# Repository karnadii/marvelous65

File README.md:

# Marvelous65 Keyboard Series
A 65% wireless hotswap keyboard with Rotary encoder, OLED display and RGB underglow.

## Marvelous65

## Marvelous65 Ergo

## Marvelous65 Split

# WARNING!!!
**FOR ADVANCED USER ONLY!!, THIS IS A DIY KEYBOARD AND NO ONE SELL IT, BUILDING THIS KEYBOARD REQUIRE YOU TO ORDER THE PCB FROM PCB MANU, SOLDER ALL THE COMPONENT YOURSELF, MAKING YOUR OWN PLATE AND CASE YOURSELF. IF YOU ONLY KNOW HOW TO ASSEMBLY A KEYBOARD, THIS IS NOT FOR YOU.**

This keyboard is inspired by luantty2's Candy BLE (https://github.com/luantty2/nRF52840-instruction). When I first saw that I was like "Beautiful! Marvelous!" but that would be nice to make that in 65%. So With no basic knowledge of electronic I brave myself to learn Kicad with the guide of https://wiki.ai03.com/. Basically this is just an nrfmicro 1.4 by Joric embedded in PCB. I also learn some basic Fusion 360 to make a keyboard case and plate.

When I finish designing this, I realize I am not he first one to design this, there is someone in zfrontier forum already done it, it is called Rainbow65, check it out https://www.zfrontier.com/app/flow/e1rpMAd9Nz75.
and there is someone planning an IC for similar layout and feature. 

## Bootloader
Before flashing the firmware, you have to flash the bootloader first. Follow the nrfmicro guide to flash the bootloader https://github.com/joric/nrfmicro/wiki/Bootloader
## Firmware
The firmware will use [ZMK](https://zmkfirmware.dev/). Basic setup ZMK firmware https://zmkfirmware.dev/docs/development/setup.
copy the firmware file to `app/boards/shields`. Edit the keymap or any other feature as you want and build the firmware using the following command 
```bash
west build -p -b nrfmicro_13 -- -DSHIELD=marvelous65_rev2
west build -p -b nrfmicro_13 -- -DSHIELD=marvelous65_ergo
west build -p -b nrfmicro_13 -- -DSHIELD=marvelous65_split_right
west build -p -b nrfmicro_13 -- -DSHIELD=marvelous65_split_left
```

## Features
- Dual mode wireless and wired
- rotary encoder
- oled display 
- rgb underglow
- hotswap (except split version)
- multilayout (except ergo version)

## PCB 
the marvelous65 standard and split version I route it manually. the ergo version I semi auto route it with freerouting. I know a little about electronic, if you have some suggestion or want to coorect the PCB/schematic feel free to make a PR or open an issue.
### Marvelous65

### Marvelous65 Ergo

### Marvelous65 Split

## Layout
### Marvelous65

try it in [KLE](http://www.keyboard-layout-editor.com/##@_name=marvelous65%3B&@_x:3%3B&=~%0A%60&=!%0A1&=%2F@%0A2&=%23%0A3&=$%0A4&=%25%0A5&=%5E%0A6&=%2F&%0A7&=*%0A8&=(%0A9&=)%0A0&=%2F_%0A-&=+%0A%2F=&_a:6&w:2%3B&=Back&_x:0.25%3B&=enc1&_x:1&a:7%3B&=&=%3B&@_x:3&a:4&w:1.5%3B&=Tab&=Q&=W&=E&=R&=T&=Y&=U&=I&=O&=P&=%7B%0A%5B&=%7D%0A%5D&_w:1.5%3B&=%7C%0A%5C&_x:3&a:7&w:1.25&h:2&w2:1.5&h2:1&x2:-0.25%3B&=%3B&@_a:4&w:1.25&w2:1.75&l:true%3B&=Caps%20Lock&_x:1.75&w:1.75%3B&=Caps%20Lock&=A&=S&=D&=F&=G&=H&=J&=K&=L&=%2F:%0A%2F%3B&=%22%0A'&_a:6&w:2.25%3B&=Enter&_x:2&a:7%3B&=%3B&@_w:1.25%3B&=&=&_x:0.75&a:6&w:2.25%3B&=Shift&_a:4%3B&=Z&=X&=C&=V&=B&=N&=M&=%3C%0A,&=%3E%0A.&=%3F%0A%2F%2F&_a:6&w:1.75%3B&=Shift%3B&@_y:-0.75&x:17.25&a:7%3B&=%E2%86%91%3B&@_y:-0.25&x:3&a:6&w:1.25%3B&=Ctrl&_w:1.25%3B&=Win&_w:1.25%3B&=Alt&_a:7&w:6.25%3B&=&_a:6%3B&=Alt&=Fn&=Ctrl%3B&@_y:-0.75&x:16.25&a:7%3B&=%E2%86%90&=%E2%86%93&=%E2%86%92%3B&@_x:6.75&w:2.25%3B&=&_w:1.25%3B&=&_w:2.75%3B&=&_w:1.5%3B&=&_w:1.5%3B&=) (Support ISO, stplit backspace, split spacebar, stepped caps)

### Marvelous65 Ergo

try it in [KLE](http://www.keyboard-layout-editor.com/##@_name=Marvelous65%20Ergo%3B&@_y:0.2&x:2.75%3B&=%2F@%0A2&_x:8.75%3B&=%2F_%0A-%3B&@_y:-0.95&x:0.75%3B&=~%0A%60&=!%0A1&_x:10.75%3B&=+%0A%2F=&_a:6&w:2%3B&=Backspace&_x:0.75%3B&=ENC%3B&@_y:-0.050000000000000044&x:12.25&a:4%3B&=P%3B&@_y:-0.9500000000000002&x:0.5&w:1.5%3B&=Tab&=Q&_x:10.25%3B&=%7B%0A%5B&=%7D%0A%5D&_w:1.5%3B&=%7C%0A%5C%3B&@_x:0.25&w:1.75%3B&=Caps%20Lock&=A&_x:9.75%3B&=%2F:%0A%2F%3B&=%22%0A'&_a:6&w:2.25%3B&=Enter%3B&@_w:2.25%3B&=Shift&_a:4%3B&=Z&_x:9%3B&=%3E%0A.&=%3F%0A%2F%2F&_a:6&w:1.75%3B&=Shift%3B&@_y:-0.75&x:16.25&a:7%3B&=%E2%86%91%3B&@_y:-0.25&a:6&w:1.25%3B&=Ctrl&_w:1.25%3B&=Win&_x:10&a:7&w:1.25%3B&=&_w:1.25%3B&=%3B&@_y:-0.75&x:15.25%3B&=%E2%86%90&=%E2%86%93&=%E2%86%92%3B&@_r:12&rx:3.05&ry:4.35&y:-1.0999999999999996&x:0.20000000000000018&a:4%3B&=X&=C&=V&=B%3B&@_x:0.20000000000000018&a:7&w:1.25%3B&=&_w:2.75%3B&=%3B&@_rx:3.15&ry:3.35&y:-1.1&x:-0.1499999999999999&a:4%3B&=S&=D&=F&=G%3B&@_rx:3.25&ry:2.35&y:-1.1&x:-0.25%3B&=W&=E&=R&=T%3B&@_rx:3.35&ry:1.35&y:-1.1&x:0.3999999999999999%3B&=%23%0A3&=$%0A4&=%25%0A5&=%5E%0A6%3B&@_r:-12&rx:12.1&y:-1.1&x:-3.5999999999999996%3B&=%2F&%0A7&=*%0A8&=(%0A9&=)%0A0%3B&@_rx:12.2&ry:2.35&y:-1.1&x:-3.9499999999999993%3B&=Y&=U&=I&=O%3B&@_rx:12.3&ry:3.35&y:-1.1&x:-3.5500000000000007%3B&=H&=J&=K&=L%3B&@_rx:12.4&ry:4.35&y:-1.0999999999999996&x:-4.15&a:7%3B&=&_a:4%3B&=N&=M&=%3C%0A,%3B&@_rx:12.525&ry:5.5415&y:-1.2915&x:-4.025&a:7&w:2.25%3B&=&_w:1.25%3B&=) (Support split backspace and stepped caps) 

### Marvelous65 Split

try in in [KLE](http://www.keyboard-layout-editor.com/##@_name=Marvelous%20split%3B&@_x:18.25&a:6&w:2%3B&=Backspace%3B&@_x:2.25%3B&=L%2F_ENC&_x:0.25&a:4%3B&=~%0A%60&=!%0A1&=%2F@%0A2&=%23%0A3&=$%0A4&=%25%0A5&=%5E%0A6&_x:1.75%3B&=%2F&%0A7&=*%0A8&=(%0A9&=)%0A0&=%2F_%0A-&=+%0A%2F=&_a:7%3B&=&=&_x:0.25&a:6%3B&=R%2F_ENC%3B&@_x:3.5&a:4&w:1.5%3B&=Tab&=Q&=W&=E&=R&=T&_x:1.75%3B&=Y&=U&=I&=O&=P&=%7B%0A%5B&=%7D%0A%5D&_w:1.5%3B&=%7C%0A%5C&_x:2.75&a:7&w:1.25&h:2&w2:1.5&h2:1&x2:-0.25%3B&=%3B&@_a:6&w:1.25&w2:1.75&l:true%3B&=Cap&_x:2.25&a:4&w:1.75%3B&=Caps%20Lock&=A&=S&=D&=F&=G&_x:1.75%3B&=H&=J&=K&=L&=%2F:%0A%2F%3B&=%22%0A'&_a:6&w:2.25%3B&=Enter&_x:1.75&a:7%3B&=%3B&@_a:6&w:2.25%3B&=Shift&_x:1.25&a:7&w:1.25%3B&=&=&_a:4%3B&=Z&=X&=C&=V&=B&_x:1.75%3B&=N&=M&=%3C%0A,&=%3E%0A.&=%3F%0A%2F%2F&_a:6&w:1.75%3B&=Shift%3B&@_y:-0.75&x:19.5&a:7%3B&=%E2%86%91%3B&@_y:-0.25&x:3.5&a:6&w:1.25%3B&=Ctrl&_w:1.25%3B&=Win&_w:1.25%3B&=Alt&_a:7&w:2.25%3B&=&_w:1.25%3B&=&_x:1.75&w:2.75%3B&=&_a:6%3B&=Alt&=Fn&=Ctrl%3B&@_y:-0.75&x:18.5&a:7%3B&=%E2%86%90&=%E2%86%93&=%E2%86%92%3B&@_x:15.25&w:1.5%3B&=&_w:1.5%3B&=) (Support ISO, stplit backspace, split spacebar, stepped caps)

## Case
All the case is all 3d printed, except the ergo version have acrylic version case. The case have 3 part, top, middle and bottom. the top and bottom using PLA with 20% infill, while the middle use transparent PLA with 100% infill(to diffuse the underglow RGB) I only know some basic 3d knowledge, so if my case is not to your liking you can design your own case and make a PR or keep it to yourself. Here some rendered Image from fusion 360. The case is top mount. Using M2x5/M2x6 threaded insert and M2 screw (I don't remember the exact size, just buy a set of m2 screw.) The plate for marvelous65 and marvelous65 ergo is sandwiched between top case and bottom case, 

### Marvelous65

### Marvelous65 Ergo
#### Acrylic case

#### 3d printed case

### Marvelous65 Split
I am too lazy while designing this one, so I only design ANSI layout case. The plate is integrated to the case, so if you want different layout you want to make another case.

## GIF

https://user-images.githubusercontent.com/18657277/117118259-c4ab1200-adba-11eb-80a2-d7a4a54a5487.mp4

https://user-images.githubusercontent.com/18657277/117118099-8dd4fc00-adba-11eb-8657-396213f3611c.mp4

## BOM
See BOM file for JLCPCB in release page.
also I added IBOM for reference when you will solder it yourself

Marvelous65 IBOM https://karnadii.github.io/marvelous65/Marvelous65/Hardware/bom/ibom.html

Marvelous65-ergo IBOM https://karnadii.github.io/marvelous65/Marvelous65-ergo/Hardware/bom/ibom.html

Marvelous65-split IBOM https://karnadii.github.io/marvelous65/Marvelous65-split/Hardware/bom/ibom.html

## Battery
any lipo battery will do, i use 2.4 JST XH connector. it is better to use 3mm thickness battery.

for the pcb [JST XH2.54 Right Angle Pin Header Connector 2P](https://www.aliexpress.com/item/33008489410.html?spm=a2g0o.productlist.0.0.3fc04e79tqtraW&algo_pvid=cc25e59e-b91b-4300-889b-37802f464f64&algo_expid=cc25e59e-b91b-4300-889b-37802f464f64-14&btsid=0bb0620316222031400651818ee7d1&ws_ab_test=searchweb0_0,searchweb201602_,searchweb201603_)
for battery [JST XH 2PIN male](https://www.aliexpress.com/item/32996835431.html?spm=a2g0o.productlist.0.0.52173629BM0hSB&algo_pvid=e2dc7462-9258-4ca2-80d9-968e44934c82&algo_expid=e2dc7462-9258-4ca2-80d9-968e44934c82-4&btsid=0bb0622f16222032556806705ee066&ws_ab_test=searchweb0_0,searchweb201602_,searchweb201603_).
All the battery that I purchase have no connector/socket, so I have to solder it myself. Be carefull when soldering, pay attention to the negative and positive of the battery.

I am using this battery. Ignore the label the actual size is 3300mAh.

## TODO
- add acrylic case version
- add multi layout case for split version
- fix ergo version plate (misaligned one screw hole)
- marvelous65 ergo 3d printed case split version
- designing logo and silkscreen
- add assembly guide

## Support Me
Help me order prototype PCB for next revision

## Reference 
- nrfmicro 1.4 https://github.com/joric/nrfmicro/wiki
- nice60 pcb https://github.com/Nicell/nice60
- ZMK firmware https://github.com/zmkfirmware/zmk

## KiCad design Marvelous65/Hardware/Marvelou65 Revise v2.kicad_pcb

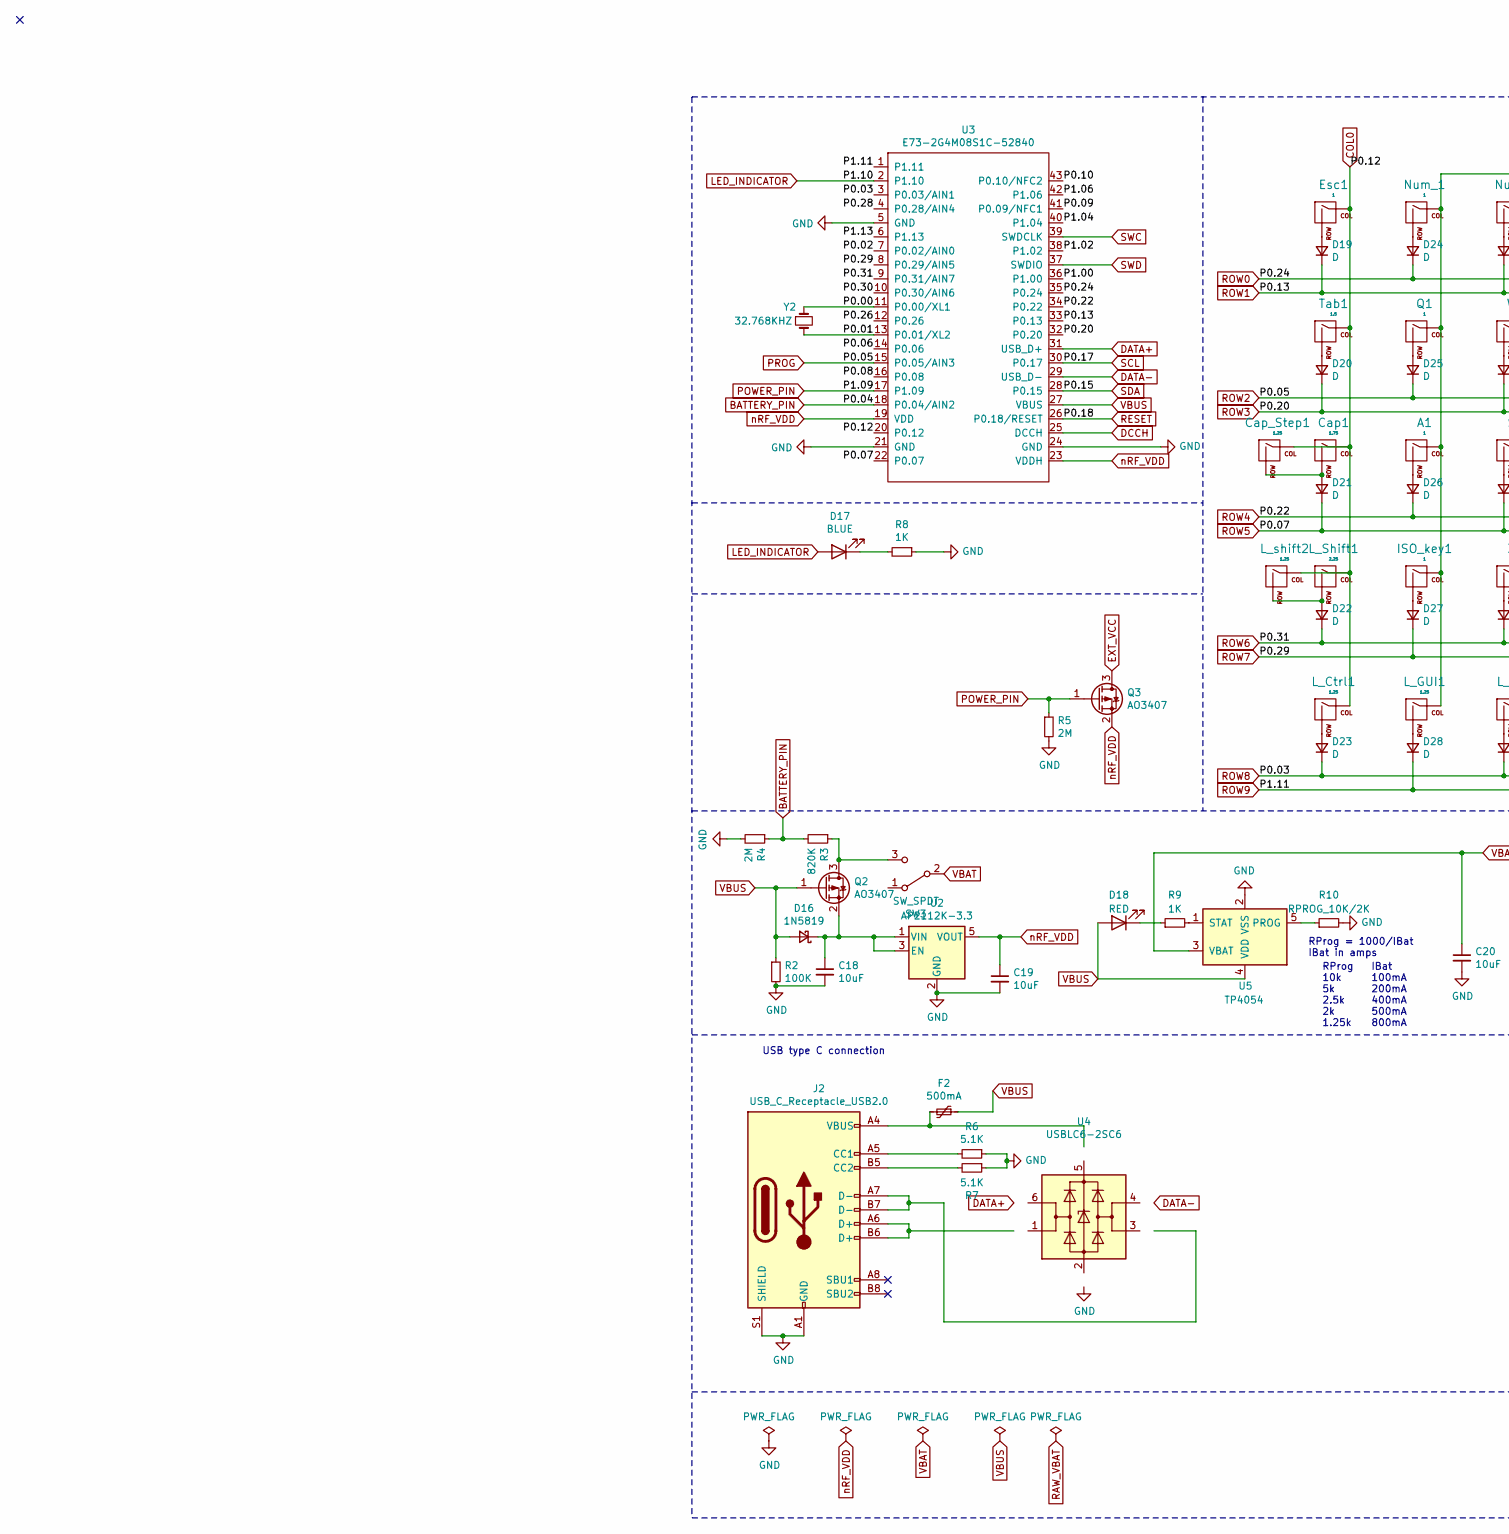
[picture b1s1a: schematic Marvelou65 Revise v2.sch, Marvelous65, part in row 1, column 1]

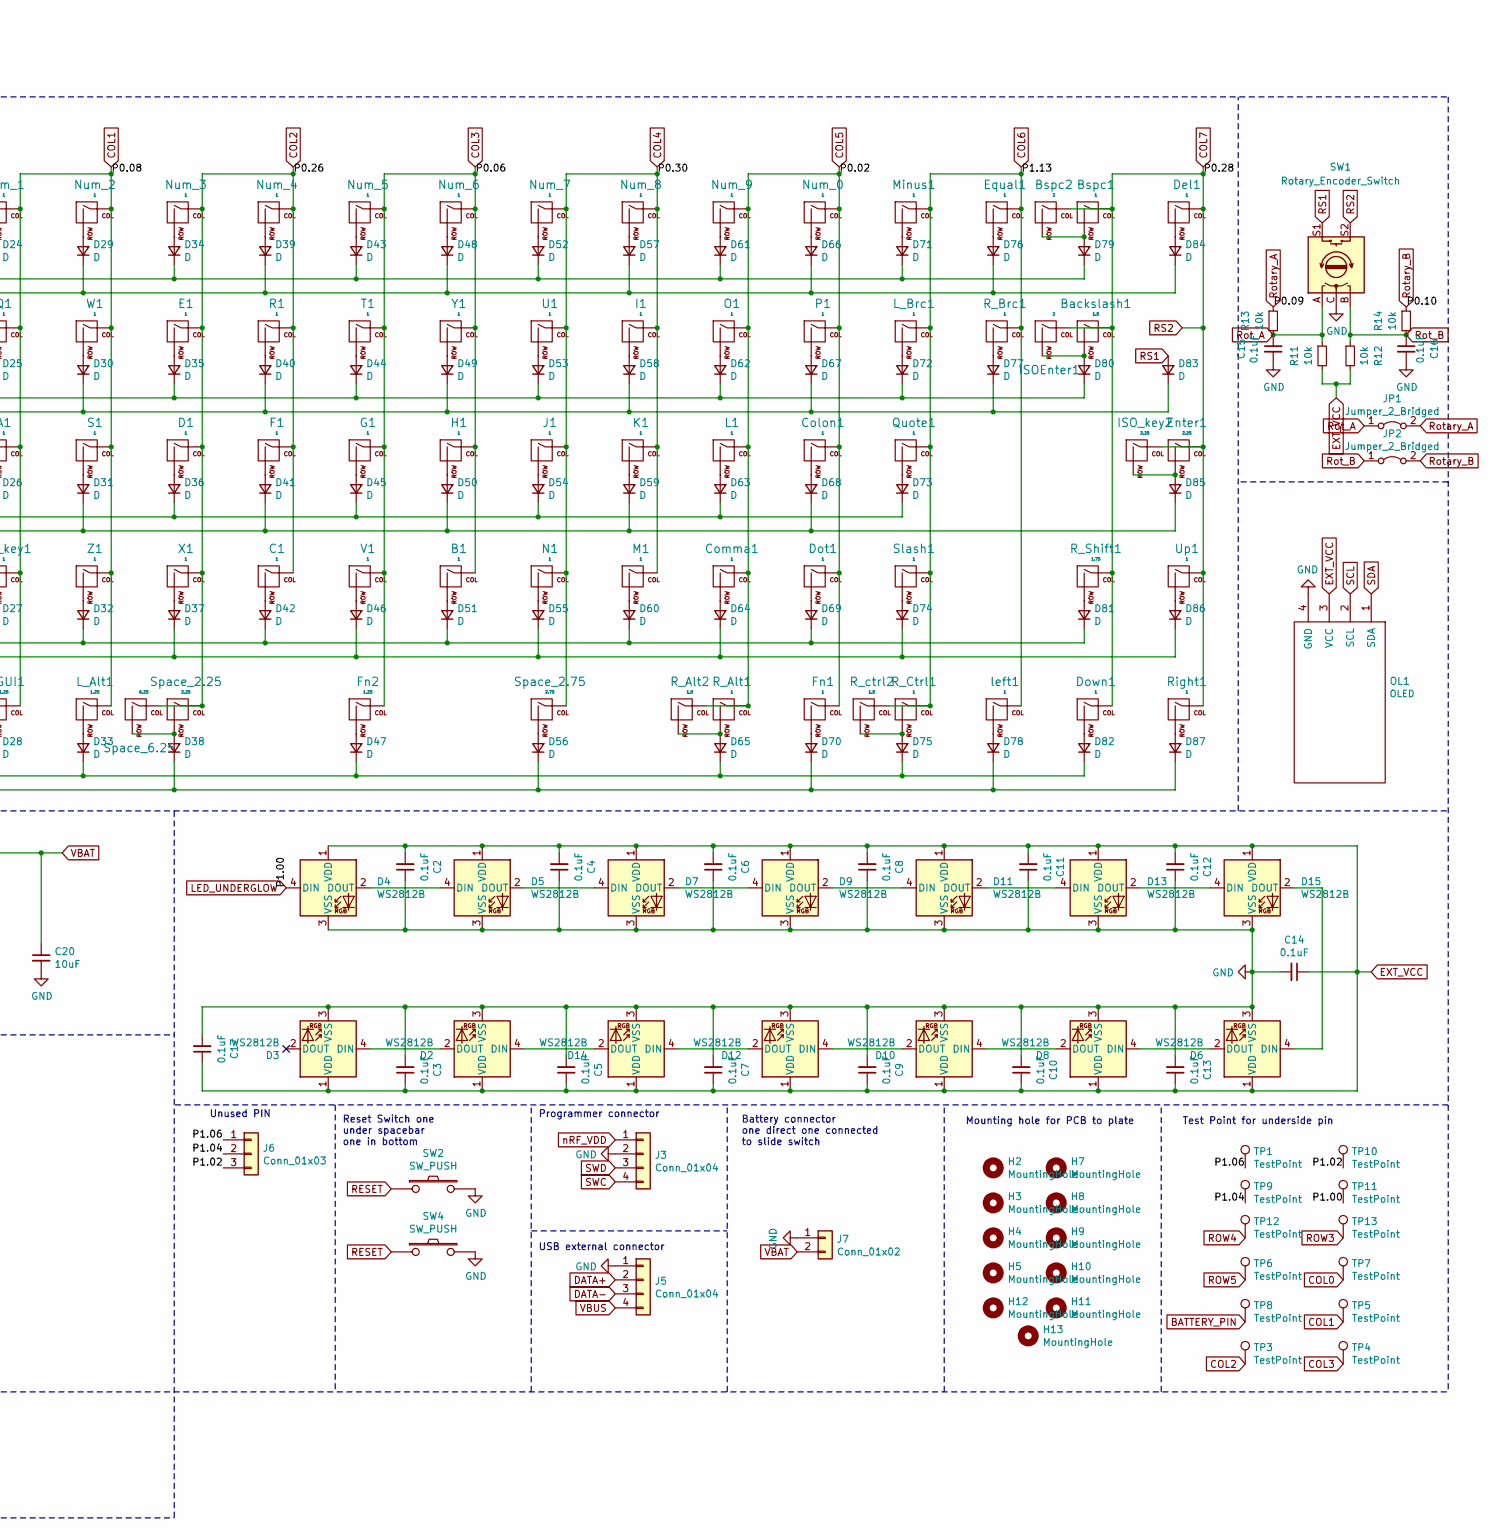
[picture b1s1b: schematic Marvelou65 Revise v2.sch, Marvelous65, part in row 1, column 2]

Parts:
A1: 1; MXOnly-1U-Hotswap
B1: 1; MXOnly-1U-Hotswap
Backslash1: 1.5; MXOnly-1.5U-Hotswap
Bspc1: 1; MXOnly-1U-Hotswap
Bspc2: 2; MXOnly-2U-Hotswap
C1: 1; MXOnly-1U-Hotswap
C2, C3, C4, C5, C6, C7, C8, C9, C10, C11, C12, C13, C14, C15, C16, C17: 0.1uF; C_0805_2012Metric_Pad1.15x1.40mm_HandSolder; LCSC Part Number C49678
C18, C19, C20: 10uF; C_0805_2012Metric_Pad1.15x1.40mm_HandSolder; LCSC Part Number C15850
Cap1: 1.75; MXOnly-1.75U-Hotswap
Cap_Step1: 1.25; MXOnly-1.25U-Hotswap
Colon1: 1; MXOnly-1U-Hotswap
Comma1: 1; MXOnly-1U-Hotswap
D1: 1; MXOnly-1U-Hotswap
D2, D3, D4, D5, D6, D7, D8, D9, D10, D11, D12, D13, D14, D15: WS2812B; LED_WS2812B_PLCC4_5.0x5.0mm_P3.2mm; LCSC Part Number C114586
D16: 1N5819; D_SOD-123; LCSC Part Number C169540
D17: BLUE; LED_0603_1608Metric_Pad1.05x0.95mm_HandSolder; LCSC Part Number C375446
D18: RED; LED_0603_1608Metric_Pad1.05x0.95mm_HandSolder; LCSC Part Number C375450
D19, D20, D21, D22, D23, D24, D25, D26, D27, D28, D29, D30, D31, D32, D33, D34, D35, D36, D37, D38, D39, D40, D41, D42, D43, D44, D45, D46, D47, D48, D49, D50, D51, D52, D53, D54, D55, D56, D57, D58, D59, D60, D61, D62, D63, D64, D65, D66, D67, D68, D69, D70, D71, D72, D73, D74, D75, D76, D77, D78, D79, D80, D81, D82, D83, D84, D85, D86, D87: D; D_SOD-123; LCSC Part Number C81598
Del1: 1; MXOnly-1U-Hotswap
Dot1: 1; MXOnly-1U-Hotswap
Down1: 1; MXOnly-1U-Hotswap
E1: 1; MXOnly-1U-Hotswap
Enter1: 2.25; MXOnly-2.25U-Hotswap
Equal1: 1; MXOnly-1U-Hotswap
Esc1: 1; MXOnly-1U-Hotswap
F1: 1; MXOnly-1U-Hotswap
F2: 500mA; Fuse_0805_2012Metric_Pad1.15x1.40mm_HandSolder; LCSC Part Number C261942
Fn1: 1; MXOnly-1U-Hotswap
Fn2: 1.25; MXOnly-1.25U-Hotswap
G1: 1; MXOnly-1U-Hotswap
H1: 1; MXOnly-1U-Hotswap
H2, H3, H4, H5, H7, H8, H9, H10, H11, H12, H13: MountingHole; MountingHole_2.2mm_M2_Pad
I1: 1; MXOnly-1U-Hotswap
ISOEnter1: 2; MXOnly-2U-Hotswap-ReversedStabilizers
ISO_key1: 1; MXOnly-1U-Hotswap
ISO_key2: 2.25; MXOnly-1U-Hotswap
J1: 1; MXOnly-1U-Hotswap
J2: USB_C_Receptacle_USB2.0; USB_C_Receptacle_HRO_TYPE-C-31-M-12; LCSC Part Number C165948
J3: Conn_01x04; connector_swd
J5: Conn_01x04; connector_usb
J6: Conn_01x03; PinSocket_1x03_P2.54mm_Vertical
J7: Conn_01x02; JST_XH_S2B-XH-A-1_1x02_P2.50mm_Horizontal; LCSC Part Number C157931
JP1, JP2: Jumper_2_Bridged; Jumper
K1: 1; MXOnly-1U-Hotswap
L1: 1; MXOnly-1U-Hotswap
L_Alt1: 1.25; MXOnly-1.25U-Hotswap
L_Brc1: 1; MXOnly-1U-Hotswap
L_Ctrl1: 1.25; MXOnly-1.25U-Hotswap
L_GUI1: 1.25; MXOnly-1.25U-Hotswap
L_Shift1: 2.25; MXOnly-2.25U-Hotswap
L_shift2: 1.25; MXOnly-1.25U-Hotswap
M1: 1; MXOnly-1U-Hotswap
Minus1: 1; MXOnly-1U-Hotswap
N1: 1; MXOnly-1U-Hotswap
Num_0, Num_1, Num_2, Num_3, Num_4, Num_5, Num_6, Num_7, Num_8, Num_9: 1; MXOnly-1U-Hotswap
O1: 1; MXOnly-1U-Hotswap
OL1: OLED
P1: 1; MXOnly-1U-Hotswap
Q1: 1; MXOnly-1U-Hotswap
Q2, Q3: AO3407; TSOT-23; LCSC Part Number C693136
Quote1: 1; MXOnly-1U-Hotswap
R1: 1; MXOnly-1U-Hotswap
R2: 100K; R_0603_1608Metric_Pad1.05x0.95mm_HandSolder; LCSC Part Number C25803
R3: 820K; R_0603_1608Metric_Pad1.05x0.95mm_HandSolder; LCSC Part Number C23252
R4, R5: 2M; R_0603_1608Metric_Pad1.05x0.95mm_HandSolder; LCSC Part Number C22976
R6, R7: 5.1K; R_0603_1608Metric_Pad1.05x0.95mm_HandSolder; LCSC Part Number C23186
R8, R9: 1K; R_0603_1608Metric_Pad1.05x0.95mm_HandSolder; LCSC Part Number C21190
R10: RPROG_10K/2K; R_0603_1608Metric_Pad1.05x0.95mm_HandSolder; LCSC Part Number C22975
R11, R12, R13, R14: 10k; R_0603_1608Metric_Pad1.05x0.95mm_HandSolder; LCSC Part Number C25804
R_Alt1: 1; MXOnly-1U-Hotswap
R_Alt2: 1.5; MXOnly-1.5U-Hotswap
R_Brc1: 1; MXOnly-1U-Hotswap
R_Ctrl1: 1; MXOnly-1U-Hotswap
R_Shift1: 1.75; MXOnly-1.75U-Hotswap
R_ctrl2: 1.5; MXOnly-1.5U-Hotswap
Right1: 1; MXOnly-1U-Hotswap
S1: 1; MXOnly-1U-Hotswap
SW1: Rotary_Encoder_Switch; RotaryEncoder_Alps_EC11E-Switch_Vertical_H20mm; LCSC Part Number C470748
SW2, SW4: SW_PUSH; SW_SPST_TL3342; LCSC Part Number C318884
SW3: SW_SPDT; SW_SPDT_PCM12; LCSC Part Number C221841
Slash1: 1; MXOnly-1U-Hotswap
Space_2.25: 2.25; MXOnly-2.25U-Hotswap-ReversedStabilizers
Space_2.75: 2.75; MXOnly-2.75U-Hotswap-ReversedStabilizers
Space_6.25: 6.25; MXOnly-6.25U-Hotswap
T1: 1; MXOnly-1U-Hotswap
TP1, TP3, TP4, TP5, TP6, TP7, TP8, TP9, TP10, TP11, TP12, TP13: TestPoint; TestPoint_Pad_D1.0mm
Tab1: 1.5; MXOnly-1.5U-Hotswap
U1: 1; MXOnly-1U-Hotswap
U2: AP2112K-3.3; SOT-23-5; LCSC Part Number C51118
U3: E73-2G4M08S1C-52840; LCSC Part Number C356849
U4: USBLC6-2SC6; SOT-23-6; LCSC Part Number C558442
U5: TP4054; SOT-23-5; LCSC Part Number C32574
Up1: 1; MXOnly-1U-Hotswap
V1: 1; MXOnly-1U-Hotswap
W1: 1; MXOnly-1U-Hotswap
X1: 1; MXOnly-1U-Hotswap
Y1: 1; MXOnly-1U-Hotswap
Y2: 32.768KHZ; Crystal_SMD_3215-2Pin_3.2x1.5mm; LCSC Part Number C479190
Z1: 1; MXOnly-1U-Hotswap
left1: 1; MXOnly-1U-Hotswap

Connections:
/P0.00: U3.11 (P0.00/XL1), Y2.1
/P0.01: U3.13 (P0.01/XL2), Y2.2
/P1.02: J6.3, TP10.1, U3.38 (P1.02)
/P1.04: J6.2, TP9.1, U3.40 (P1.04)
/P1.06: J6.1, TP1.1, U3.42 (P1.06)
BATTERY_PIN: R3.2, R4.1, TP8.1, U3.18 (P0.04/AIN2)
COL0: Cap1.1 (COL), Cap_Step1.1 (COL), Esc1.1 (COL), L_Ctrl1.1 (COL), L_Shift1.1 (COL), L_shift2.1 (COL), TP7.1, Tab1.1 (COL), U3.20 (P0.12)
COL1: A1.1 (COL), ISO_key1.1 (COL), L_Alt1.1 (COL), L_GUI1.1 (COL), Num_1.1 (COL), Num_2.1 (COL), Q1.1 (COL), S1.1 (COL), TP5.1, U3.16 (P0.08), W1.1 (COL), Z1.1 (COL)
COL2: C1.1 (COL), D1.1 (COL), E1.1 (COL), F1.1 (COL), Num_3.1 (COL), Num_4.1 (COL), R1.1 (COL), Space_2.25.1 (COL), Space_6.25.1 (COL), TP3.1, U3.12 (P0.26), X1.1 (COL)
COL3: B1.1 (COL), Fn2.1 (COL), G1.1 (COL), H1.1 (COL), Num_5.1 (COL), Num_6.1 (COL), T1.1 (COL), TP4.1, U3.14 (P0.06), V1.1 (COL), Y1.1 (COL)
COL4: I1.1 (COL), J1.1 (COL), K1.1 (COL), M1.1 (COL), N1.1 (COL), Num_7.1 (COL), Num_8.1 (COL), Space_2.75.1 (COL), U1.1 (COL), U3.10 (P0.30/AIN6)
COL5: Colon1.1 (COL), Comma1.1 (COL), Dot1.1 (COL), Fn1.1 (COL), L1.1 (COL), Num_0.1 (COL), Num_9.1 (COL), O1.1 (COL), P1.1 (COL), R_Alt1.1 (COL), R_Alt2.1 (COL), U3.7 (P0.02/AIN0)
COL6: Equal1.1 (COL), L_Brc1.1 (COL), Minus1.1 (COL), Quote1.1 (COL), R_Brc1.1 (COL), R_Ctrl1.1 (COL), R_ctrl2.1 (COL), Slash1.1 (COL), U3.6 (P1.13), left1.1 (COL)
COL7: Backslash1.1 (COL), Bspc1.1 (COL), Bspc2.1 (COL), Del1.1 (COL), Down1.1 (COL), Enter1.1 (COL), ISOEnter1.1 (COL), ISO_key2.1 (COL), R_Shift1.1 (COL), Right1.1 (COL), SW1.S2, U3.4 (P0.28/AIN4), Up1.1 (COL)
DATA+: J5.2, U3.31 (USB_D+)
DATA-: J5.3, U3.29 (USB_D-)
DCCH: U3.25 (DCCH)
EXT_VCC: C2.2, C3.1, C4.2, C5.1, C6.2, C7.1, C8.2, C9.1, C10.1, C11.2, C12.2, C13.1, C14.1, C17.1, D2.1 (VDD), D3.1 (VDD), D4.1 (VDD), D5.1 (VDD), D6.1 (VDD), D7.1 (VDD), D8.1 (VDD), D9.1 (VDD), D10.1 (VDD), D11.1 (VDD), D12.1 (VDD), D13.1 (VDD), D14.1 (VDD), D15.1 (VDD), OL1.3 (VCC), Q3.3 (D), R11.2, R12.2
GND: C2.1, C3.2, C4.1, C5.2, C6.1, C7.2, C8.1, C9.2, C10.2, C11.1, C12.1, C13.2, C14.2, C15.2, C16.2, C17.2, C18.2, C19.2, C20.2, D2.3 (VSS), D3.3 (VSS), D4.3 (VSS), D5.3 (VSS), D6.3 (VSS), D7.3 (VSS), D8.3 (VSS), D9.3 (VSS), D10.3 (VSS), D11.3 (VSS), D12.3 (VSS), D13.3 (VSS), D14.3 (VSS), D15.3 (VSS), J2.A1 (GND), J2.A12 (GND), J2.B1 (GND), J2.B12 (GND), J2.S1 (SHIELD), J3.2, J5.1, J7.1, OL1.4 (GND), R2.2, R4.2, R5.2, R6.1, R7.1, R8.1, R10.2, SW1.C, SW2.2, SW4.2, U2.2 (GND), U3.5 (GND), U3.21 (GND), U3.24 (GND), U5.2 (VSS)
LED_INDICATOR: D17.2 (A), U3.2 (P1.10)
LED_UNDERGLOW: D4.4 (DIN), TP11.1, U3.36 (P1.00)
unnamed: A1.2 (ROW), D26.2 (A)
unnamed: B1.2 (ROW), D51.2 (A)
unnamed: Backslash1.2 (ROW), D80.2 (A), ISOEnter1.2 (ROW)
unnamed: Bspc1.2 (ROW), Bspc2.2 (ROW), D79.2 (A)
unnamed: C1.2 (ROW), D42.2 (A)
unnamed: C18.1, D16.1 (K), Q2.2 (S), U2.1 (VIN), U2.3 (EN)
unnamed: Cap1.2 (ROW), Cap_Step1.2 (ROW), D21.2 (A)
unnamed: Colon1.2 (ROW), D68.2 (A)
unnamed: Comma1.2 (ROW), D64.2 (A)
unnamed: D1.2 (ROW), D36.2 (A)
unnamed: D2.2 (DOUT), D3.4 (DIN)
unnamed: D4.2 (DOUT), D5.4 (DIN)
unnamed: D5.2 (DOUT), D7.4 (DIN)
unnamed: D6.2 (DOUT), D8.4 (DIN)
unnamed: D7.2 (DOUT), D9.4 (DIN)
unnamed: D10.2 (DOUT), D12.4 (DIN)
unnamed: D8.2 (DOUT), D10.4 (DIN)
unnamed: D11.2 (DOUT), D13.4 (DIN)
unnamed: D9.2 (DOUT), D11.4 (DIN)
unnamed: D12.2 (DOUT), D14.4 (DIN)
unnamed: D13.2 (DOUT), D15.4 (DIN)
unnamed: D2.4 (DIN), D14.2 (DOUT)
unnamed: D6.4 (DIN), D15.2 (DOUT)
unnamed: D17.1 (K), R8.2
unnamed: D18.1 (K), R9.1
unnamed: D19.2 (A), Esc1.2 (ROW)
unnamed: D20.2 (A), Tab1.2 (ROW)
unnamed: D22.2 (A), L_Shift1.2 (ROW), L_shift2.2 (ROW)
unnamed: D23.2 (A), L_Ctrl1.2 (ROW)
unnamed: D24.2 (A), Num_1.2 (ROW)
unnamed: D25.2 (A), Q1.2 (ROW)
unnamed: D27.2 (A), ISO_key1.2 (ROW)
unnamed: D28.2 (A), L_GUI1.2 (ROW)
unnamed: D29.2 (A), Num_2.2 (ROW)
unnamed: D30.2 (A), W1.2 (ROW)
unnamed: D31.2 (A), S1.2 (ROW)
unnamed: D32.2 (A), Z1.2 (ROW)
unnamed: D33.2 (A), L_Alt1.2 (ROW)
unnamed: D34.2 (A), Num_3.2 (ROW)
unnamed: D35.2 (A), E1.2 (ROW)
unnamed: D37.2 (A), X1.2 (ROW)
unnamed: D38.2 (A), Space_2.25.2 (ROW), Space_6.25.2 (ROW)
unnamed: D39.2 (A), Num_4.2 (ROW)
unnamed: D40.2 (A), R1.2 (ROW)
unnamed: D41.2 (A), F1.2 (ROW)
unnamed: D43.2 (A), Num_5.2 (ROW)
unnamed: D44.2 (A), T1.2 (ROW)
unnamed: D45.2 (A), G1.2 (ROW)
unnamed: D46.2 (A), V1.2 (ROW)
unnamed: D47.2 (A), Fn2.2 (ROW)
unnamed: D48.2 (A), Num_6.2 (ROW)
unnamed: D49.2 (A), Y1.2 (ROW)
unnamed: D50.2 (A), H1.2 (ROW)
unnamed: D52.2 (A), Num_7.2 (ROW)
unnamed: D53.2 (A), U1.2 (ROW)
unnamed: D54.2 (A), J1.2 (ROW)
unnamed: D55.2 (A), N1.2 (ROW)
unnamed: D56.2 (A), Space_2.75.2 (ROW)
unnamed: D57.2 (A), Num_8.2 (ROW)
unnamed: D58.2 (A), I1.2 (ROW)
unnamed: D59.2 (A), K1.2 (ROW)
unnamed: D60.2 (A), M1.2 (ROW)
unnamed: D61.2 (A), Num_9.2 (ROW)
unnamed: D62.2 (A), O1.2 (ROW)
unnamed: D63.2 (A), L1.2 (ROW)
unnamed: D65.2 (A), R_Alt1.2 (ROW), R_Alt2.2 (ROW)
unnamed: D66.2 (A), Num_0.2 (ROW)
unnamed: D67.2 (A), P1.2 (ROW)
unnamed: D69.2 (A), Dot1.2 (ROW)
unnamed: D70.2 (A), Fn1.2 (ROW)
unnamed: D71.2 (A), Minus1.2 (ROW)
unnamed: D72.2 (A), L_Brc1.2 (ROW)
unnamed: D73.2 (A), Quote1.2 (ROW)
unnamed: D74.2 (A), Slash1.2 (ROW)
unnamed: D75.2 (A), R_Ctrl1.2 (ROW), R_ctrl2.2 (ROW)
unnamed: D76.2 (A), Equal1.2 (ROW)
unnamed: D77.2 (A), R_Brc1.2 (ROW)
unnamed: D78.2 (A), left1.2 (ROW)
unnamed: D81.2 (A), R_Shift1.2 (ROW)
unnamed: D82.2 (A), Down1.2 (ROW)
unnamed: D84.2 (A), Del1.2 (ROW)
unnamed: D85.2 (A), Enter1.2 (ROW), ISO_key2.2 (ROW)
unnamed: D86.2 (A), Up1.2 (ROW)
unnamed: D87.2 (A), Right1.2 (ROW)
unnamed: F2.2, J2.A4 (VBUS), J2.A9 (VBUS), J2.B4 (VBUS), J2.B9 (VBUS)
unnamed: J2.A5 (CC1), R6.2
unnamed: J2.A6 (D+), J2.B6 (D+)
unnamed: J2.A7 (D-), J2.B7 (D-)
unnamed: J2.B5 (CC2), R7.2
unnamed: Q2.3 (D), R3.1, SW3.3 (C)
unnamed: R9.2, U5.1 (STAT)
unnamed: R10.1, U5.5 (PROG)
POWER_PIN: Q3.1 (G), R5.1, U3.17 (P1.09)
PROG: D25.1 (K), D35.1 (K), D44.1 (K), D53.1 (K), D62.1 (K), D72.1 (K), D80.1 (K), U3.15 (P0.05/AIN3)
RESET: SW2.1, SW4.1, U3.26 (P0.18/RESET)
ROW0: D24.1 (K), D34.1 (K), D43.1 (K), D52.1 (K), D61.1 (K), D71.1 (K), D79.1 (K), U3.35 (P0.24)
ROW1: D19.1 (K), D29.1 (K), D39.1 (K), D48.1 (K), D57.1 (K), D66.1 (K), D76.1 (K), D84.1 (K), U3.33 (P0.13)
ROW3: D20.1 (K), D30.1 (K), D40.1 (K), D49.1 (K), D58.1 (K), D67.1 (K), D77.1 (K), D83.1 (K), TP13.1, U3.32 (P0.20)
ROW4: D26.1 (K), D36.1 (K), D45.1 (K), D54.1 (K), D63.1 (K), D73.1 (K), TP12.1, U3.34 (P0.22)
ROW5: D21.1 (K), D31.1 (K), D41.1 (K), D50.1 (K), D59.1 (K), D68.1 (K), D85.1 (K), TP6.1, U3.22 (P0.07)
ROW6: D22.1 (K), D32.1 (K), D42.1 (K), D51.1 (K), D60.1 (K), D69.1 (K), D81.1 (K), U3.9 (P0.31/AIN7)
ROW7: D27.1 (K), D37.1 (K), D46.1 (K), D55.1 (K), D64.1 (K), D74.1 (K), D86.1 (K), U3.8 (P0.29/AIN5)
ROW8: D23.1 (K), D33.1 (K), D47.1 (K), D65.1 (K), D75.1 (K), D82.1 (K), U3.3 (P0.03/AIN1)
ROW9: D28.1 (K), D38.1 (K), D56.1 (K), D70.1 (K), D78.1 (K), D87.1 (K), U3.1 (P1.11)
RS1: D83.2 (A), SW1.S1
Rot_A: C15.1, JP1.1 (A), R11.1, R13.2, SW1.A
Rot_B: C16.1, JP2.1 (A), R12.1, R14.2, SW1.B
Rotary_A: JP1.2 (B), R13.1, U3.41 (P0.09/NFC1)
Rotary_B: JP2.2 (B), R14.1, U3.43 (P0.10/NFC2)
SCL: OL1.2 (SCL), U3.30 (P0.17)
SDA: OL1.1 (SDA), U3.28 (P0.15)
SWC: J3.4, U3.39 (SWDCLK)
SWD: J3.3, U3.37 (SWDIO)
VBAT: C20.1, J7.2, SW3.2 (B), U5.3 (VBAT)
VBUS: D16.2 (A), D18.2 (A), F2.1, J5.4, Q2.1 (G), R2.1, U3.27 (VBUS), U5.4 (VDD)
nRF_VDD: C19.1, J3.1, Q3.2 (S), U2.5 (VOUT), U3.19 (VDD), U3.23 (VDDH)

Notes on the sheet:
RProg = 1000/IBat IBat in amps
RProg 10k 5k 2.5k 2k 1.25k
IBat 100mA 200mA 400mA 500mA 800mA
Test Point for underside pin
Mounting hole for PCB to plate
Battery connector one direct one connected to slide switch
Programmer connector
USB external connector
Reset Switch one under spacebar one in bottom
Unused PIN
USB type C connection

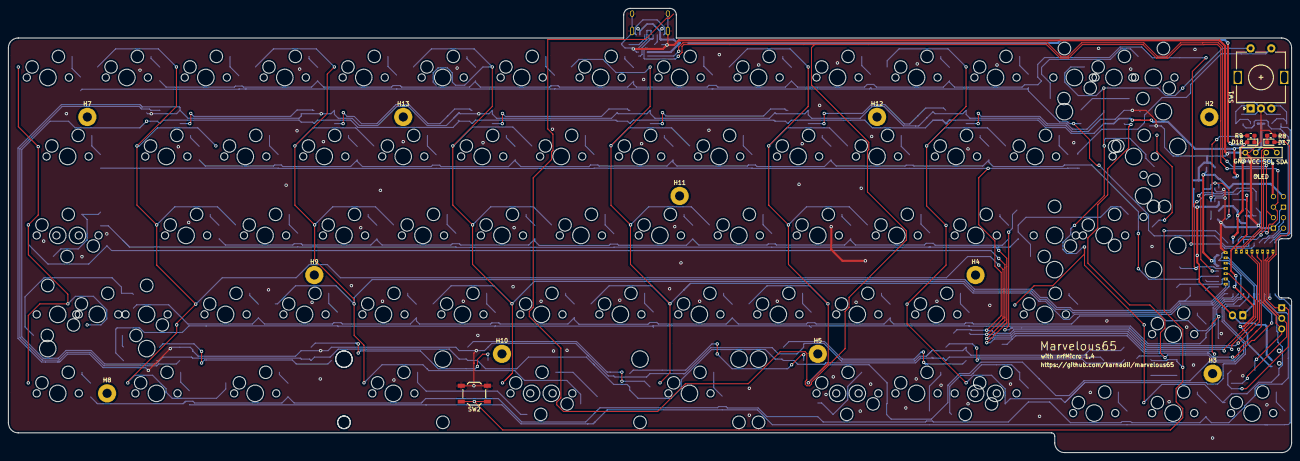
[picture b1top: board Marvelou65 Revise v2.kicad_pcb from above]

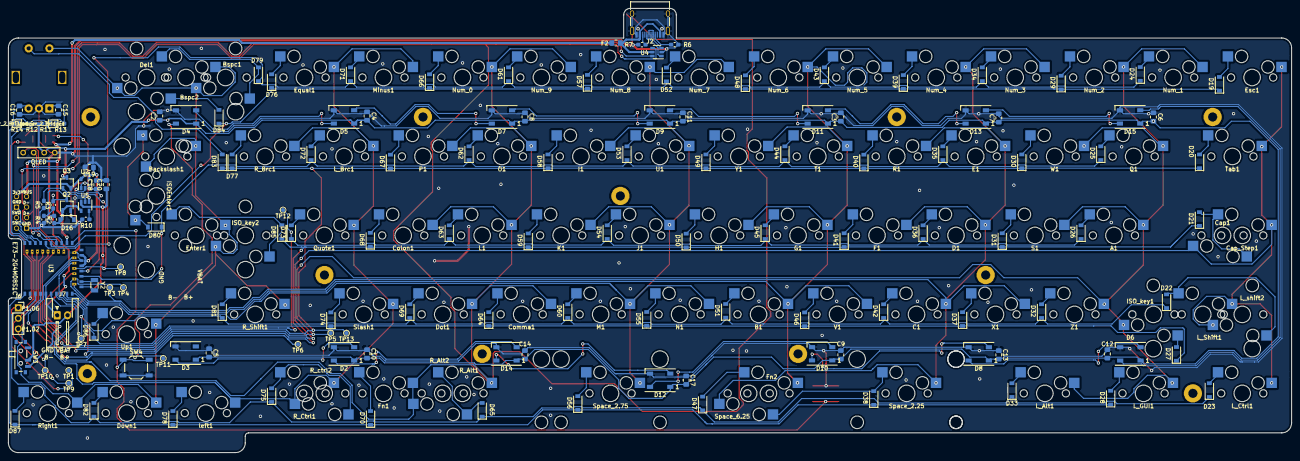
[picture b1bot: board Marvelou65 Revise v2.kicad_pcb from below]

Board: 2 copper layers, 309.6 x 107.2 mm, 237 parts (141 on the bottom side), 136 nets.

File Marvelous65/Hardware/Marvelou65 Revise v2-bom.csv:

Comment,Designator,Footprint,LCSC
"2","Bspc2","MX_Only:MXOnly-2U-Hotswap",""
"10uF","C18,C19,C20","Capacitor_SMD:C_0805_2012Metric_Pad1.15x1.40mm_HandSolder","C15850"
"0.1uF","C2,C3,C4,C5,C6,C7,C8,C9,C10,C11,C12,C13,C14,C15,C16,C17","Capacitor_SMD:C_0805_2012Metric_Pad1.15x1.40mm_HandSolder","C49678"
"WS2812B","D2,D3,D4,D5,D6,D7,D8,D9,D10,D11,D12,D13,D14,D15","LED_SMD:LED_WS2812B_PLCC4_5.0x5.0mm_P3.2mm","C114586"
"1N5819","D16","Diode_SMD:D_SOD-123","C169540"
"BLUE","D17","LED_SMD:LED_0603_1608Metric_Pad1.05x0.95mm_HandSolder","C375446"
"RED","D18","LED_SMD:LED_0603_1608Metric_Pad1.05x0.95mm_HandSolder","C375450"
"D","D19,D20,D21,D22,D23,D24,D25,D26,D27,D28,D29,D30,D31,D32,D33,D34,D35,D36,D37,D38,D39,D40,D41,D42,D43,D44,D45,D46,D47,D48,D49,D50,D51,D52,D53,D54,D55,D56,D57,D58,D59,D60,D61,D62,D63,D64,D65,D66,D67,D68,D69,D70,D71,D72,D73,D74,D75,D76,D77,D78,D79,D80,D81,D82,D83,D84,D85,D86,D87","Diode_SMD:D_SOD-123","C81598"
"2.25","Enter1,L_Shift1","MX_Only:MXOnly-2.25U-Hotswap",""
"1","Num_0,Esc1,Num_1,Minus1,Equal1,Bspc1,Del1,Q1,W1,E1,R1,T1,Y1,U1,I1,O1,P1,L_Brc1,R_Brc1,S1,D1,F1,G1,H1,J1,K1,L1,Colon1,Quote1,Z1,X1,C1,V1,B1,N1,M1,Comma1,Dot1,Slash1,Up1,Down1,Right1,left1,R_Ctrl1,Fn1,R_Alt1,ISO_key1,A1,Num_2,Num_3,Num_4,Num_5,Num_6,Num_7,Num_8,Num_9","MX_Only:MXOnly-1U-Hotswap",""
"500mA","F2","Fuse:Fuse_0805_2012Metric_Pad1.15x1.40mm_HandSolder","C261942"
"1.25","L_Ctrl1,L_GUI1,L_Alt1,Cap_Step1,Fn2,L_shift2","MX_Only:MXOnly-1.25U-Hotswap",""
"MountingHole","H2,H3,H4,H5,H7,H8,H9,H10,H11,H12,H13","MountingHole:MountingHole_2.2mm_M2_Pad",""
"2","ISOEnter1","MX_Only:MXOnly-2U-Hotswap-ReversedStabilizers",""
"2.25","ISO_key2","MX_Only:MXOnly-1U-Hotswap",""
"USB_C_Receptacle_USB2.0","J2","Connector_USB:USB_C_Receptacle_HRO_TYPE-C-31-M-12","C165948"
"Conn_01x04","J3","nrfmicro:connector_swd",""
"Conn_01x04","J5","nrfmicro:connector_usb",""
"Conn_01x03","J6","Connector_PinSocket_2.54mm:PinSocket_1x03_P2.54mm_Vertical",""
"Conn_01x02","J7","Connector_JST:JST_XH_S2B-XH-A-1_1x02_P2.50mm_Horizontal","C157931"
"Jumper_2_Bridged","JP1,JP2","SofleKeyboard-footprint:Jumper",""
"OLED","OL1","kbd:OLED",""
"AO3407","Q2,Q3","Package_TO_SOT_SMD:TSOT-23","C693136"
"RPROG_10K/2K","R10","Resistor_SMD:R_0603_1608Metric_Pad1.05x0.95mm_HandSolder","C22975"
"10k","R11,R12,R13,R14","Resistor_SMD:R_0603_1608Metric_Pad1.05x0.95mm_HandSolder","C25804"
"100K","R2","Resistor_SMD:R_0603_1608Metric_Pad1.05x0.95mm_HandSolder","C25803"
"820K","R3","Resistor_SMD:R_0603_1608Metric_Pad1.05x0.95mm_HandSolder","C23252"
"2M","R4,R5","Resistor_SMD:R_0603_1608Metric_Pad1.05x0.95mm_HandSolder","C22976"
"5.1K","R6,R7","Resistor_SMD:R_0603_1608Metric_Pad1.05x0.95mm_HandSolder","C23186"
"1K","R8,R9","Resistor_SMD:R_0603_1608Metric_Pad1.05x0.95mm_HandSolder","C21190"
"1.75","R_Shift1,Cap1","MX_Only:MXOnly-1.75U-Hotswap",""
"Rotary_Encoder_Switch","SW1","Rotary_Encoder:RotaryEncoder_Alps_EC11E-Switch_Vertical_H20mm","C470748"
"SW_PUSH","SW2,SW4","Button_Switch_SMD:SW_SPST_TL3342","C318884"
"SW_SPDT","SW3","Button_Switch_SMD:SW_SPDT_PCM12","C221841"
"2.25","Space_2.25","MX_Only:MXOnly-2.25U-Hotswap-ReversedStabilizers",""
"2.75","Space_2.75","MX_Only:MXOnly-2.75U-Hotswap-ReversedStabilizers",""
"6.25","Space_6.25","MX_Only:MXOnly-6.25U-Hotswap",""
"TestPoint","TP1,TP3,TP4,TP5,TP6,TP7,TP8,TP9,TP10,TP11,TP12,TP13","TestPoint:TestPoint_Pad_D1.0mm",""
"1.5","Tab1,Backslash1,R_ctrl2,R_Alt2","MX_Only:MXOnly-1.5U-Hotswap",""
"AP2112K-3.3","U2","Package_TO_SOT_SMD:SOT-23-5","C51118"
"E73-2G4M08S1C-52840","U3","nrfmicro:E73-2G4M08S1C-52840","C356849"
"USBLC6-2SC6","U4","Package_TO_SOT_SMD:SOT-23-6","C558442"
"TP4054","U5","Package_TO_SOT_SMD:SOT-23-5","C32574"
"32.768KHZ","Y2","Crystal:Crystal_SMD_3215-2Pin_3.2x1.5mm","C479190"
